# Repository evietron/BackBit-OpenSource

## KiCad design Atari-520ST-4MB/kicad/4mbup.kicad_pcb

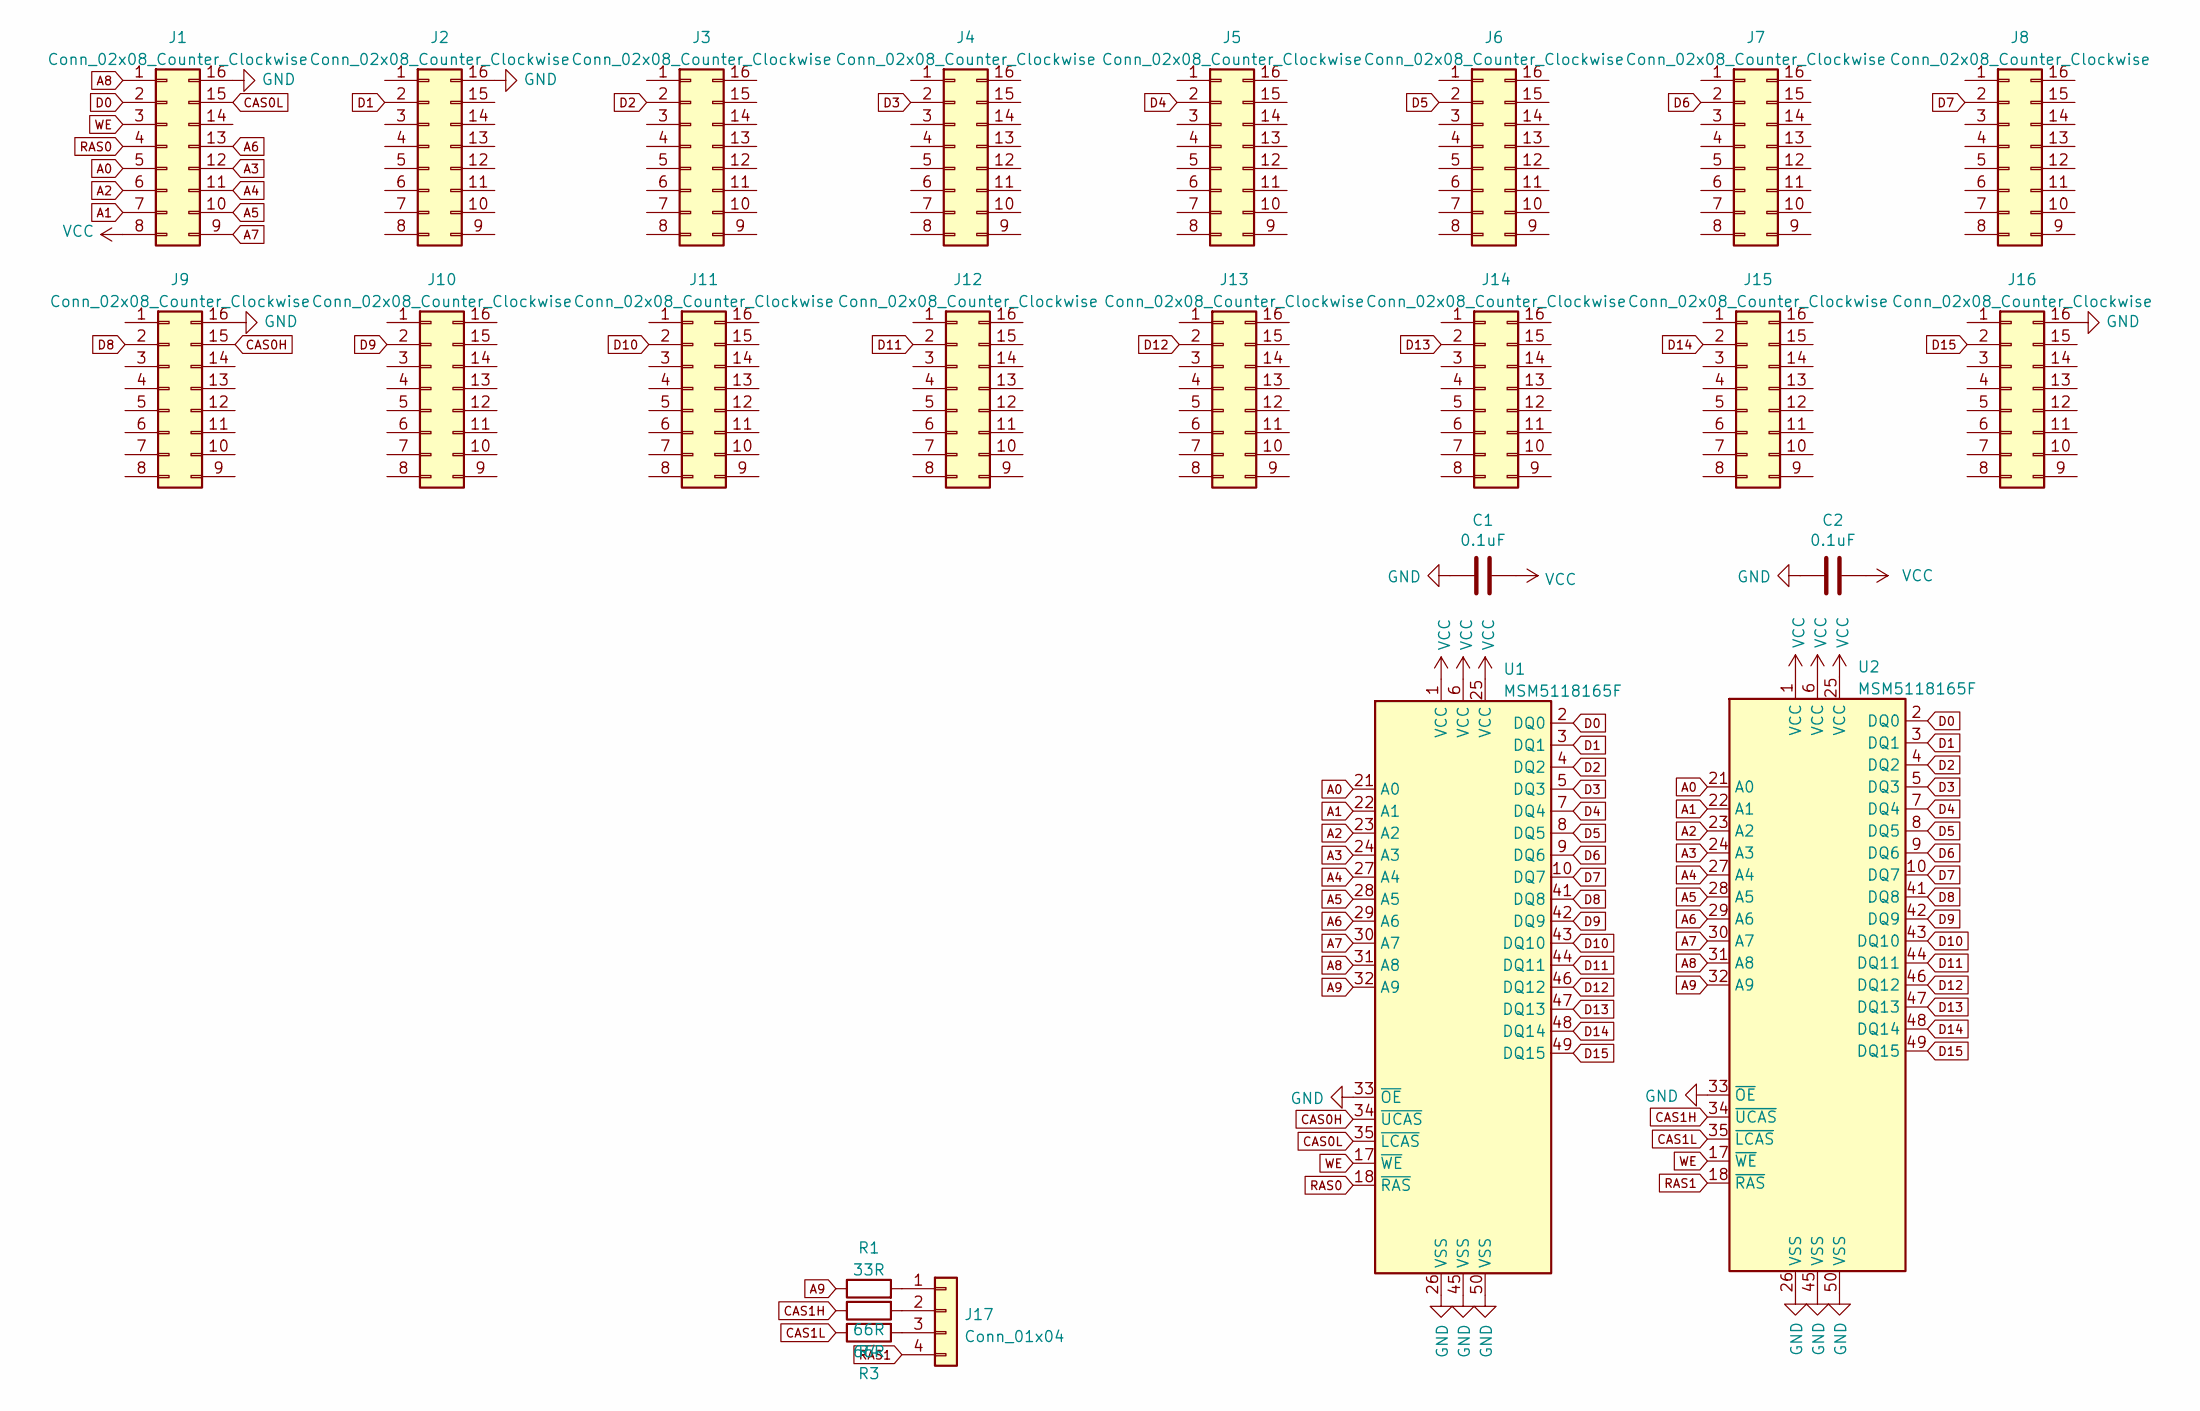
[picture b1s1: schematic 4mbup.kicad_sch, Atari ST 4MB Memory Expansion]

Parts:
C1, C2: 0.1uF; C_1206_3216Metric
J1, J9, J16: Conn_02x08_Counter_Clockwise; DIP-16_W7.62mm_SMALL_HOLES
J2, J3, J4, J5, J6, J7, J8, J10, J11, J12, J13, J14, J15: Conn_02x08_Counter_Clockwise; DIP-16-TOP_2_ROWS_W7.62mm
J17: Conn_01x04; PinHeader_1x04_P2.54mm_Vertical
R1: 33R; R_Axial_DIN0207_L6.3mm_D2.5mm_P7.62mm_Horizontal
R3, R4: 66R; R_Axial_DIN0207_L6.3mm_D2.5mm_P7.62mm_Horizontal
U1, U2: MSM5118165F; TSOP-II-50_44_10.16x18.41mm_P0.8mm_HandSolder

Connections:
A0: J1.5, U1.21 (A0), U2.21 (A0)
A1: J1.7, U1.22 (A1), U2.22 (A1)
A2: J1.6, U1.23 (A2), U2.23 (A2)
A3: J1.12, U1.24 (A3), U2.24 (A3)
A4: J1.11, U1.27 (A4), U2.27 (A4)
A5: J1.10, U1.28 (A5), U2.28 (A5)
A6: J1.13, U1.29 (A6), U2.29 (A6)
A7: J1.9, U1.30 (A7), U2.30 (A7)
A8: J1.1, U1.31 (A8), U2.31 (A8)
A9: R1.1, U1.32 (A9), U2.32 (A9)
CAS0H: J9.15, U1.34 (~UCAS)
CAS0L: J1.15, U1.35 (~LCAS)
CAS1H: R4.1, U2.34 (~UCAS)
CAS1L: R3.1, U2.35 (~LCAS)
D0: J1.2, U1.2 (DQ0), U2.2 (DQ0)
D1: J2.2, U1.3 (DQ1), U2.3 (DQ1)
D2: J3.2, U1.4 (DQ2), U2.4 (DQ2)
D3: J4.2, U1.5 (DQ3), U2.5 (DQ3)
D4: J5.2, U1.7 (DQ4), U2.7 (DQ4)
D5: J6.2, U1.8 (DQ5), U2.8 (DQ5)
D6: J7.2, U1.9 (DQ6), U2.9 (DQ6)
D7: J8.2, U1.10 (DQ7), U2.10 (DQ7)
D8: J9.2, U1.41 (DQ8), U2.41 (DQ8)
D9: J10.2, U1.42 (DQ9), U2.42 (DQ9)
D10: J11.2, U1.43 (DQ10), U2.43 (DQ10)
D11: J12.2, U1.44 (DQ11), U2.44 (DQ11)
D12: J13.2, U1.46 (DQ12), U2.46 (DQ12)
D13: J14.2, U1.47 (DQ13), U2.47 (DQ13)
D14: J15.2, U1.48 (DQ14), U2.48 (DQ14)
D15: J16.2, U1.49 (DQ15), U2.49 (DQ15)
GND: C1.2, C2.2, J1.16, J2.16, J9.16, J16.16, U1.26 (VSS), U1.33 (~OE), U1.45 (VSS), U1.50 (VSS), U2.26 (VSS), U2.33 (~OE), U2.45 (VSS), U2.50 (VSS)
unnamed: J17.1, R1.2
unnamed: J17.2, R4.2
unnamed: J17.3, R3.2
RAS0: J1.4, U1.18 (~RAS)
RAS1: J17.4, U2.18 (~RAS)
VCC: C1.1, C2.1, J1.8, U1.1 (VCC), U1.6 (VCC), U1.25 (VCC), U2.1 (VCC), U2.6 (VCC), U2.25 (VCC)
WE: J1.3, U1.17 (~WE), U2.17 (~WE)

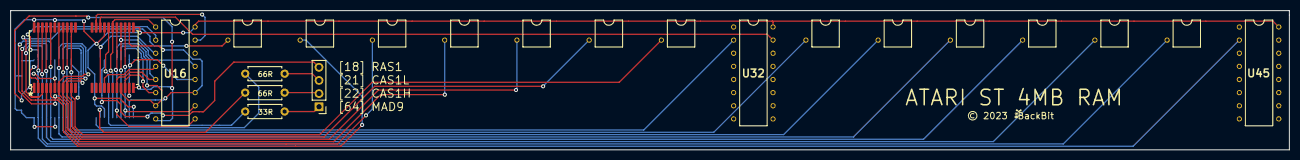
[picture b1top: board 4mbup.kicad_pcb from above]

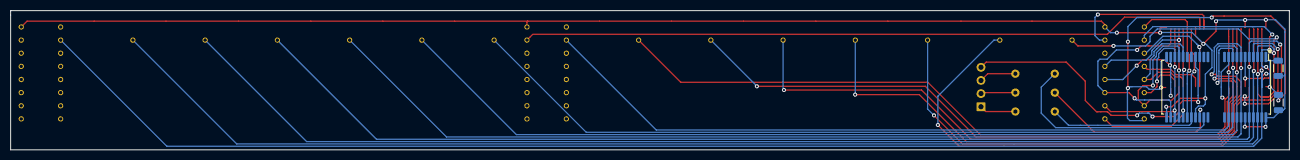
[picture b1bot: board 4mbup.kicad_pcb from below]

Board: 2 copper layers, 247.3 x 26.9 mm, 24 parts (3 on the bottom side), 38 nets.

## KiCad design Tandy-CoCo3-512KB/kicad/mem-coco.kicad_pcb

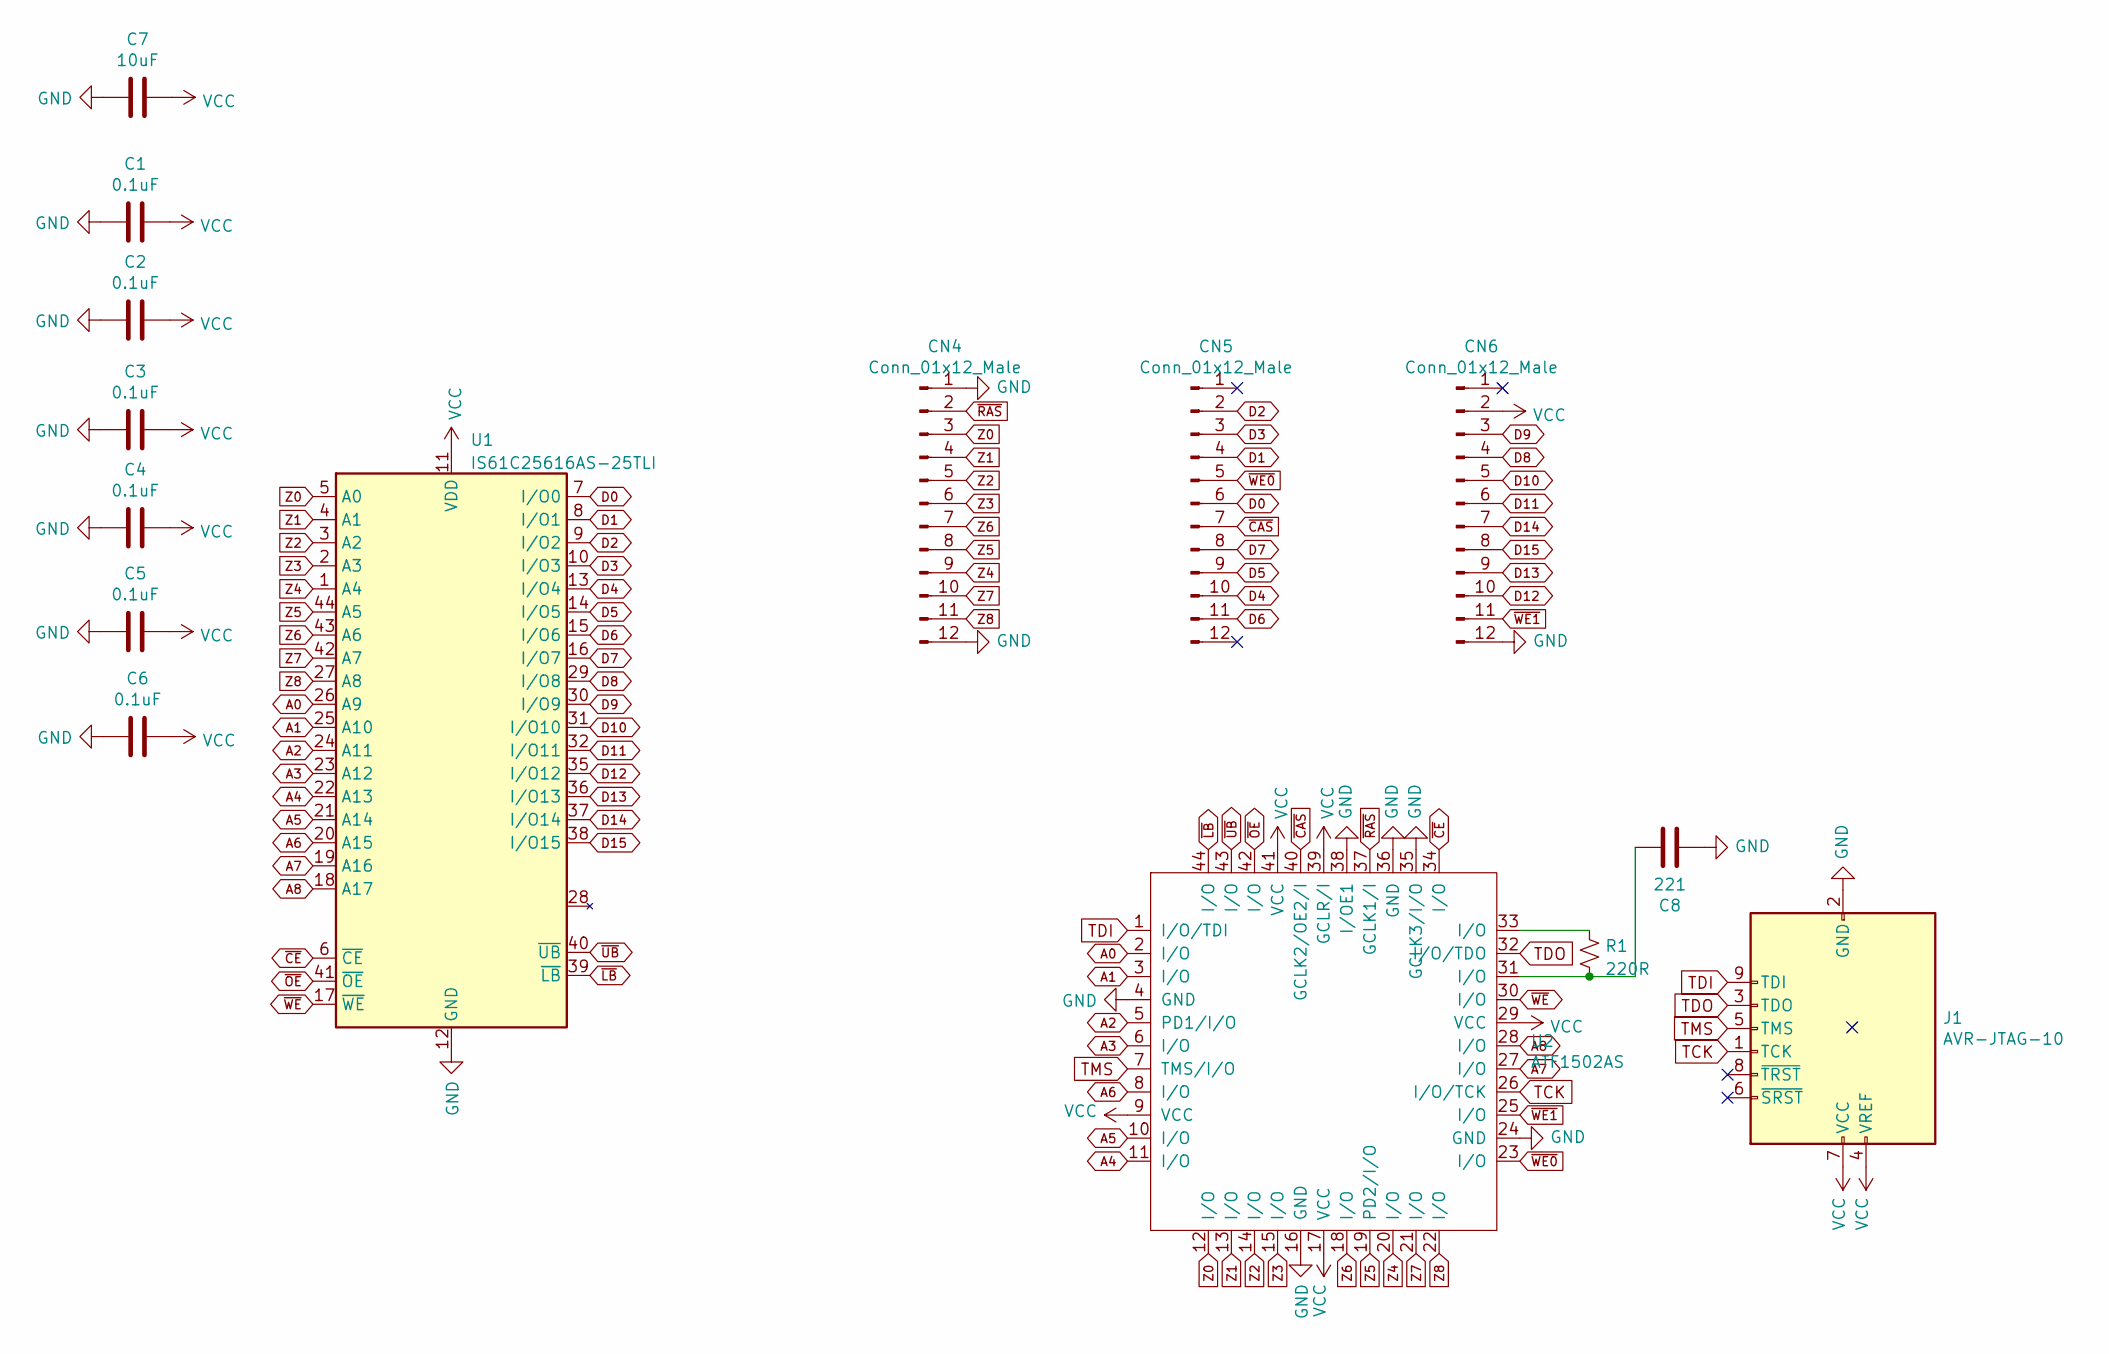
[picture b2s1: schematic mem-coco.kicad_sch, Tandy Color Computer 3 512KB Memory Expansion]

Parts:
C1, C2, C3, C4, C5, C6: 0.1uF; C_1206_3216Metric_Pad1.33x1.80mm_HandSolder
C7: 10uF; CP_Radial_D5.0mm_P2.50mm
C8: 221; C_0805_2012Metric_Pad1.18x1.45mm_HandSolder
CN4, CN5, CN6: Conn_01x12_Male; PinHeader_1x12_P2.54mm_Vertical
J1: AVR-JTAG-10; PinHeader_2x05_P2.54mm_Vertical
R1: 220R; R_0805_2012Metric_Pad1.20x1.40mm_HandSolder
U1: IS61C25616AS-25TLI; TSOP-II-44_10.16x18.41mm_P0.8mm
U2: ATF1502AS; TQFP-44_10x10mm_P0.8mm

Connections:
A0: U1.26 (A9), U2.2 (I/O)
A1: U1.25 (A10), U2.3 (I/O)
A2: U1.24 (A11), U2.5 (PD1/I/O)
A3: U1.23 (A12), U2.6 (I/O)
A4: U1.22 (A13), U2.11 (I/O)
A5: U1.21 (A14), U2.10 (I/O)
A6: U1.20 (A15), U2.8 (I/O)
A7: U1.19 (A16), U2.27 (I/O)
A8: U1.18 (A17), U2.28 (I/O)
D0: CN5.6, U1.7 (I/O0)
D1: CN5.4, U1.8 (I/O1)
D2: CN5.2, U1.9 (I/O2)
D3: CN5.3, U1.10 (I/O3)
D4: CN5.10, U1.13 (I/O4)
D5: CN5.9, U1.14 (I/O5)
D6: CN5.11, U1.15 (I/O6)
D7: CN5.8, U1.16 (I/O7)
D8: CN6.4, U1.29 (I/O8)
D9: CN6.3, U1.30 (I/O9)
D10: CN6.5, U1.31 (I/O10)
D11: CN6.6, U1.32 (I/O11)
D12: CN6.10, U1.35 (I/O12)
D13: CN6.9, U1.36 (I/O13)
D14: CN6.7, U1.37 (I/O14)
D15: CN6.8, U1.38 (I/O15)
GND: C1.2, C2.2, C3.2, C4.2, C5.2, C6.2, C7.2, C8.2, CN4.1, CN4.12, CN6.12, J1.2 (GND), J1.10 (GND), U1.12 (GND), U1.34 (GND), U2.4 (GND), U2.16 (GND), U2.24 (GND), U2.35 (GCLK3/I/O), U2.36 (GND), U2.38 (I/OE1)
unnamed: C8.1, R1.2, U2.31 (I/O)
unnamed: R1.1, U2.33 (I/O)
TCK: J1.1 (TCK), U2.26 (I/O/TCK)
TDI: J1.9 (TDI), U2.1 (I/O/TDI)
TDO: J1.3 (TDO), U2.32 (I/O/TDO)
TMS: J1.5 (TMS), U2.7 (TMS/I/O)
VCC: C1.1, C2.1, C3.1, C4.1, C5.1, C6.1, C7.1, CN6.2, J1.4 (VREF), J1.7 (VCC), U1.11 (VDD), U1.33 (VDD), U2.9 (VCC), U2.17 (VCC), U2.29 (VCC), U2.39 (GCLR/I), U2.41 (VCC)
Z0: CN4.3, U1.5 (A0), U2.12 (I/O)
Z1: CN4.4, U1.4 (A1), U2.13 (I/O)
Z2: CN4.5, U1.3 (A2), U2.14 (I/O)
Z3: CN4.6, U1.2 (A3), U2.15 (I/O)
Z4: CN4.9, U1.1 (A4), U2.20 (I/O)
Z5: CN4.8, U1.44 (A5), U2.19 (PD2/I/O)
Z6: CN4.7, U1.43 (A6), U2.18 (I/O)
Z7: CN4.10, U1.42 (A7), U2.21 (I/O)
Z8: CN4.11, U1.27 (A8), U2.22 (I/O)
~CAS: CN5.7, U2.40 (GCLK2/OE2/I)
~CE: U1.6 (~CE), U2.34 (I/O)
~LB: U1.39 (~LB), U2.44 (I/O)
~OE: U1.41 (~OE), U2.42 (I/O)
~RAS: CN4.2, U2.37 (GCLK1/I)
~UB: U1.40 (~UB), U2.43 (I/O)
~WE0: CN5.5, U2.23 (I/O)
~WE1: CN6.11, U2.25 (I/O)
~WE: U1.17 (~WE), U2.30 (I/O)

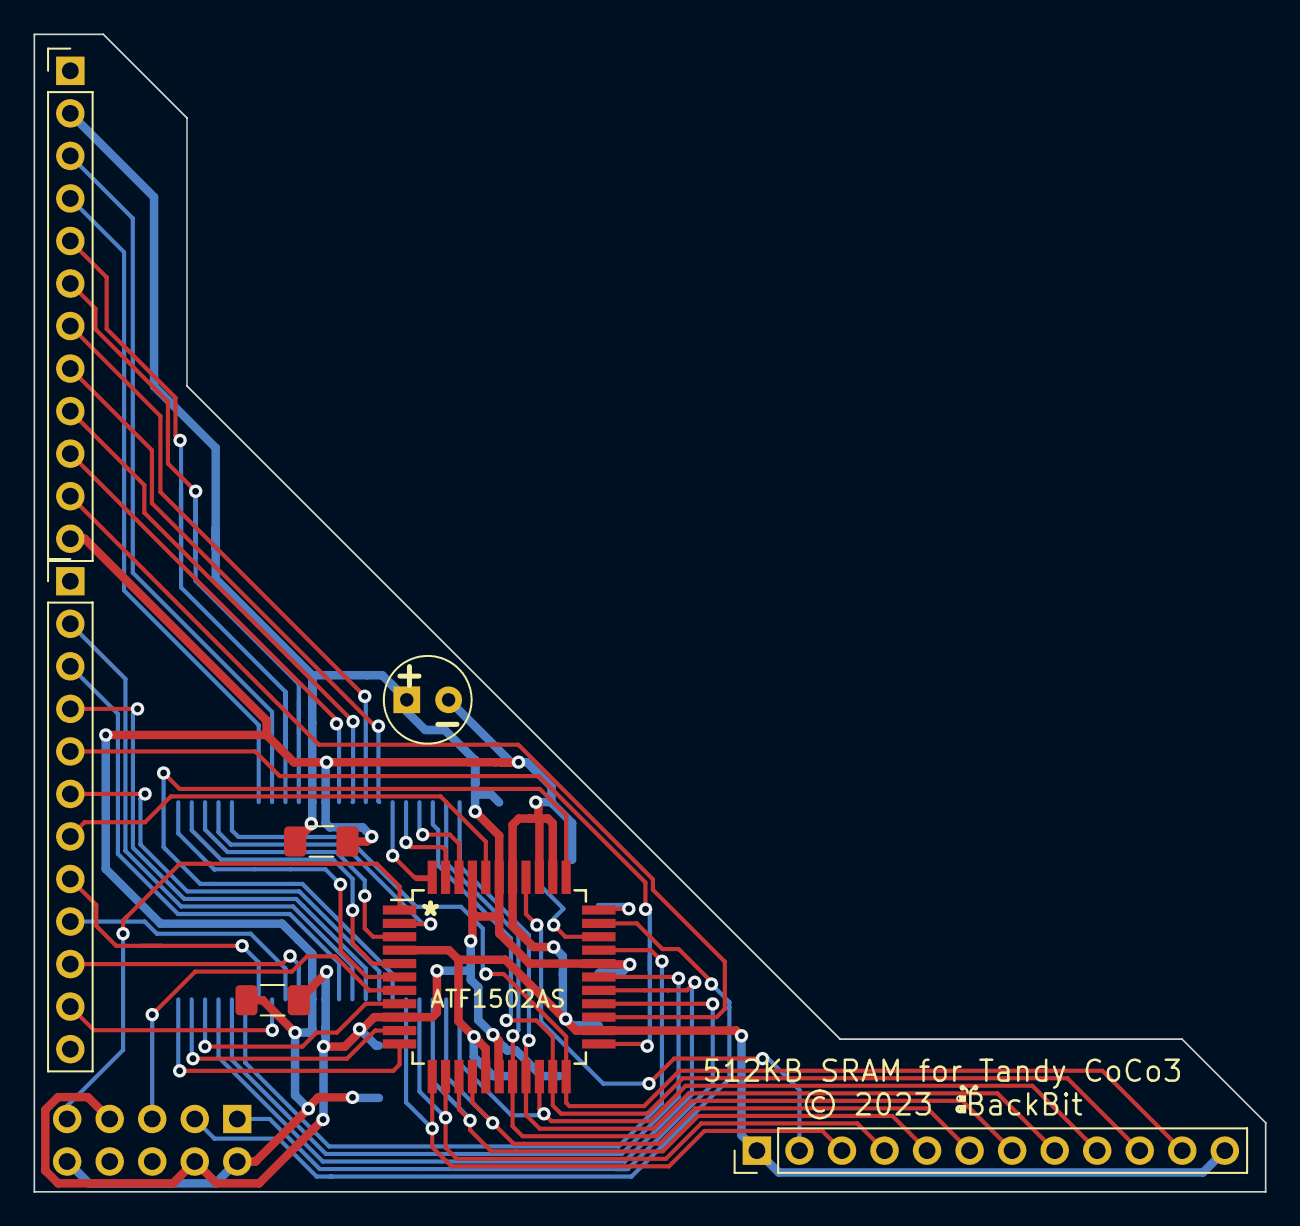
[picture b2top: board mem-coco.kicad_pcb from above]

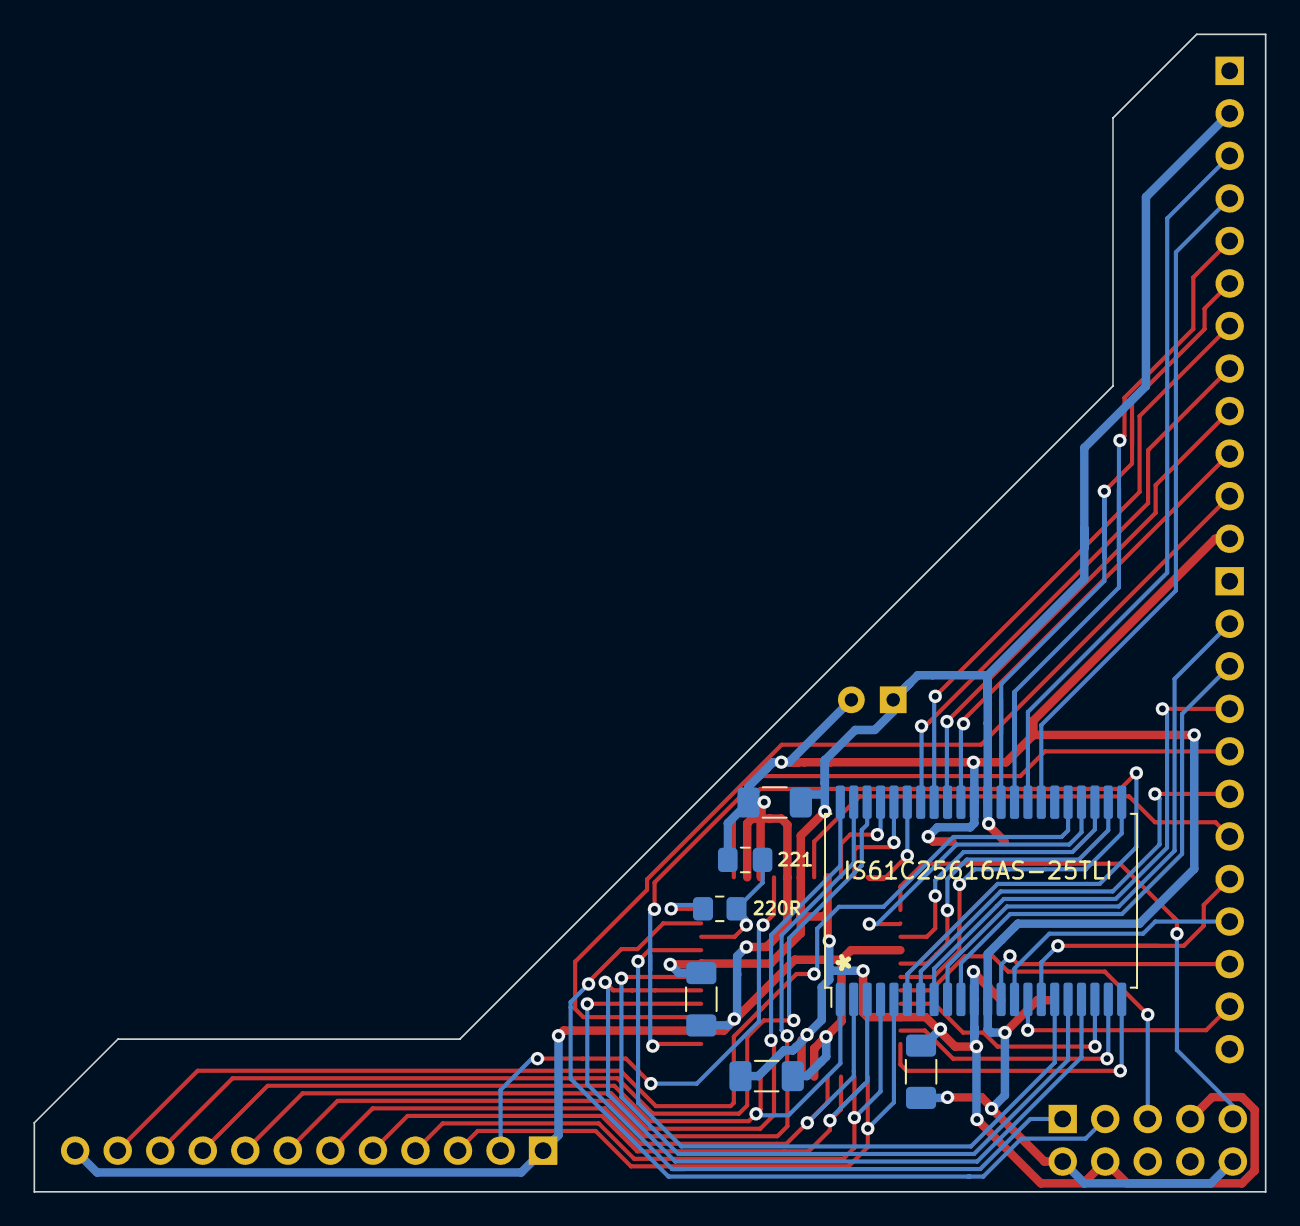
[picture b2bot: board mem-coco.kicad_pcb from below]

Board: 2 copper layers, 73.5 x 69.1 mm, 15 parts (7 on the bottom side), 51 nets.

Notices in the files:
Atari-520ST-4MB/kicad/4mbup.kicad_pcb:
© 2023  BackBit
